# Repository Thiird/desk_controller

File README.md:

# Desk Controller

Desk controller is a gadget that connects to my pc and can:
- power on/off the pc
- reset the pc
- select the booting OS
- control a bias lighting system
- control a desk led strip

The power on/off functionality is achieved by shorting the two respective pc signals to pc ground via optocouplers.

The booting OS selection is done by interacting with GRUB via serial port.

The bias lighting is the most complex part of this whole system.
The setup consists of a WS2815 12V led strip mounted around my main monitor, which is controlled by the STM32C0 of the desk controller by bit-banging the RGB data.
The RGB data is computed by a Visual C++ application running on windows and sent to the desk controller via serial port.
The main challenge here was to make a fast enough algorithm to to compute the RGB data, for the bias lighting to be reactive I wanted to achieve a 30Hz refresh rate of the RGB data, which means updating the leds color at most every 0.33.. seconds.
Without getting into GPU shaders and such, the wastest way to capture a screenshot of the screen and calculate the average color for the sections of the screen around the border, was to use the Desktop Duplication Windows API.

I inted too use this feature only during gaming or watching films, which I only do on windows. A Linux-equivalent application can always be made at a later moment,

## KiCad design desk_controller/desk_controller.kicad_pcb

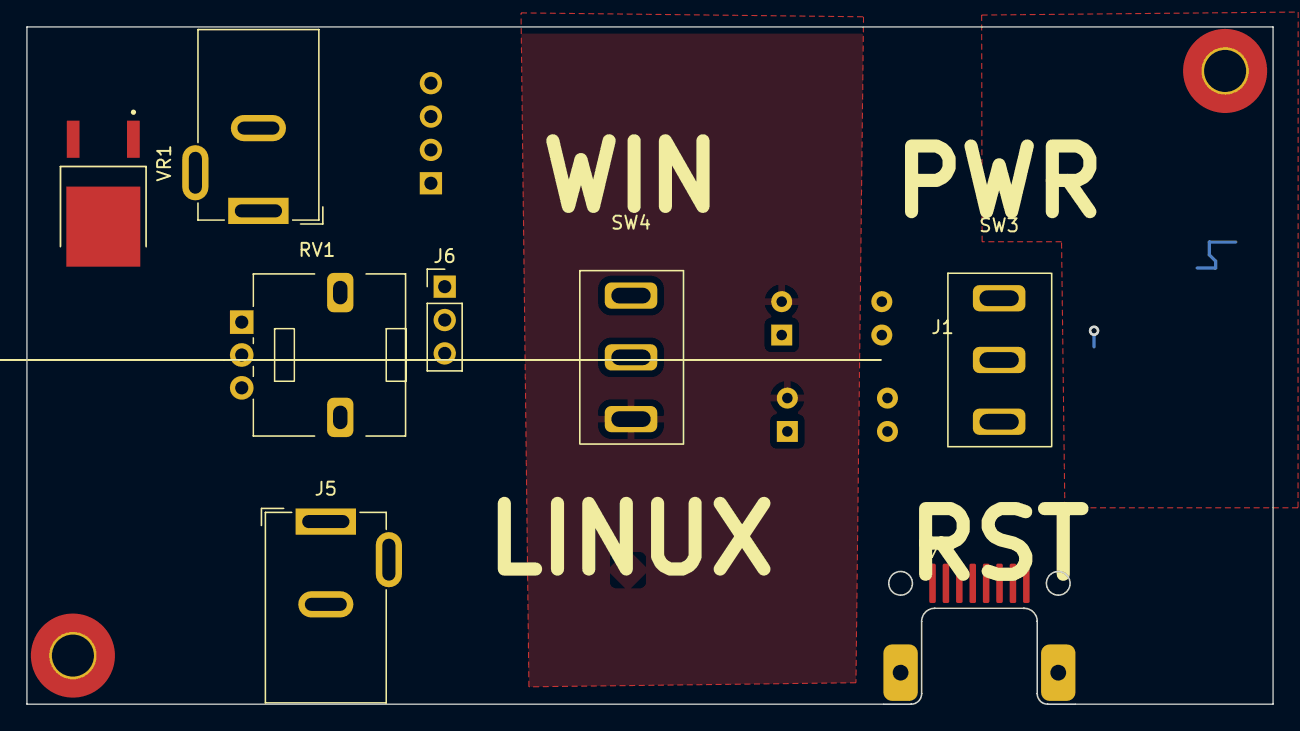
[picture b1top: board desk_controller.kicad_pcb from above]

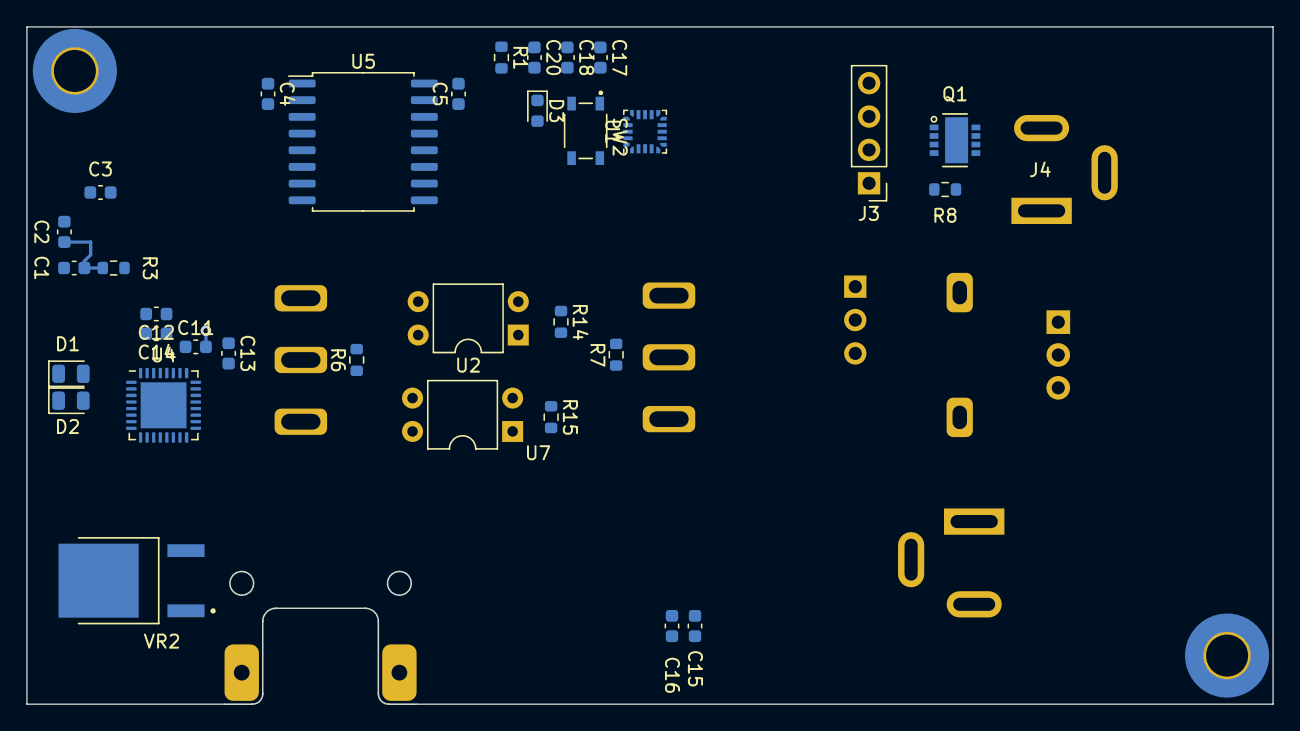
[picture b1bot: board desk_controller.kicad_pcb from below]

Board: 2 copper layers, 94.9 x 51.6 mm, 43 parts (33 on the bottom side), 36 nets.

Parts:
C1: DNP; C_0603_1608Metric
C2: 330n; C_0603_1608Metric
C3, C4, C5, C11, C12, C13, C14, C17, C18: 100n; C_0603_1608Metric
C15, C16: C; C_0603_1608Metric
C20: 4u7; C_0603_1608Metric
D1, D2: D_Schottky; D_0805_2012Metric
D3: RED; LED_0603_1608Metric
H1, H2: MountingHole; MountingHole_3.2mm_M3_Pad_TopBottom
J1: RJ45; RJ45_midplane
J3: SWD_header; PinHeader_1x04_P2.54mm_Vertical
J4, J5: Barrel_Jack_MountingPin; BarrelJack_GCT_DCJ200-10-A_Horizontal
J6: debug_uart; PinHeader_1x03_P2.54mm_Vertical
Q1: RQ3E110AJ; SOTFL65P330X80-8N
R1: 3k3; R_0603_1608Metric
R3, R6, R7: 1k; R_0603_1608Metric
R8: 10k; R_0603_1608Metric
R14, R15: R; R_0603_1608Metric
RV1: R_Potentiometer; Potentiometer_Alps_RK09L_Single_Vertical
SW2: SW_Push_Open_Dual; SW_SKRPACE010
SW3: PC_PWR_RST_SW; MTS-102-103
SW4: OS_SW; MTS-102-103
U1: STM32C011F4Ux; ST_UFQFPN-20_3x3mm_P0.5mm
U2, U7: PC817; DIP-4_W7.62mm
U4: TRS3243ECRHBR; VQFN-32-1EP_5x5mm_P0.5mm_EP3.5x3.5mm
U5: ISO7341FC; SOIC-16W_7.5x10.3mm_P1.27mm
VR1, VR2: UA78M33CKVURG3; TO229P990X252-3N

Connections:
+3.3V: C5.2, C15.1, U5.10 (EN2), U5.16 (VCC2), VR1.3 (OUT)
+3V3: C17.1, C20.1, J3.1, SW3.1, SW4.1, U1.2 (VDD)
+12V: C16.1, J4.1, J5.1, VR1.1 (IN)
/mcu/NRST: C18.1, SW2.1, SW2.2, U1.4 (PF2)
/rs232/232_DTR: D1.2 (A), J1.6, U4.2 (RIN2)
/rs232/232_RTS: D2.2 (A), J1.7, U4.3 (RIN3)
/rs232/232_RX: J1.5, U4.6 (DOUT1)
/rs232/232_TX: J1.4, U4.1 (RIN1)
/rs232/232_VCC_3V3: C3.1, C4.1, C11.1, U4.26 (VCC), U5.1 (VCC1), U5.7 (EN1), VR2.3 (OUT)
/rs232/232_VUR: C1.1, C2.1, R3.1, VR2.1 (IN)
/rs232/TTL_DTR: U4.17 (ROUT2), U5.4 (INB)
/rs232/TTL_RTS: U4.15 (ROUT3), U5.5 (INC)
/rs232/TTL_RX: U4.12 (DIN1), U5.6 (OUTD)
/rs232/TTL_TX: U4.18 (ROUT1), U5.3 (INA)
GND: C5.1, C15.2, C16.2, C17.2, C18.2, C20.2, D3.1 (K), J3.4, J5.2, J6.3, Q1.1 (S), R8.2, SW2.3, SW2.4, SW3.3, SW4.3, U1.3 (VSS), U2.2, U5.9 (GND2), U5.15 (GND2), U7.2, VR1.4 (GND)
GND1: C1.2, C2.2, C3.2, C4.2, C11.2, J1.8, U4.24 (GND), U5.2 (GND1), U5.8 (GND1), VR2.4 (GND)
unnamed: D1.1 (K), D2.1 (K), R3.2
unnamed: D3.2 (A), R1.2
unnamed: J4.2, Q1.3 (D)
unnamed: R6.2, SW3.2
unnamed: R7.2, SW4.2
unnamed: R14.2, U2.1
unnamed: R15.2, U7.1
unnamed: R1.1, U1.19 (PB7)
unnamed: C13.1, U4.28 (C1+)
unnamed: C13.2, U4.23 (C1-)
unnamed: C14.1, U4.29 (C2+)
unnamed: C14.2, U4.30 (C2-)
unnamed: C12.1, U4.27 (V+)
unnamed: C12.2, U4.31 (V-)
PC_GND: J1.3, U2.3, U7.3
PC_POWER: J1.1, U2.4
PC_RESET: J1.2, U7.4
TTL_RX_ISO: U1.15 (PA10/PA12), U5.11 (IND)
TTL_TX_ISO: U1.14 (PA9/PA11), U5.14 (OUTA)
mosfet_gate: Q1.2 (G), R8.1

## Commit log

2023-01-22 Some work
2023-01-22 Sch work
2023-01-23 Added sheets in sch, added TI document for isolated rs232 interface with power harvesting, general sch work
2023-01-25 Added components
2023-01-26 Buck converter sch, rs232 transceiver
2023-01-27 Sch fixes, initial board layout
2023-01-28 Removed acdc brick
2023-02-05 Much progress in sch and brd
2023-03-03 moved to kicad 7, sch work
2023-03-12 Added README, high level folders, working example of bias lighting calculator
2023-03-12 Edited .gitignore to remove useless heavy visual studio files
